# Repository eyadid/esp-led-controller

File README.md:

For more details visit - https://hackaday.io/project/8365-led-matrix-controller

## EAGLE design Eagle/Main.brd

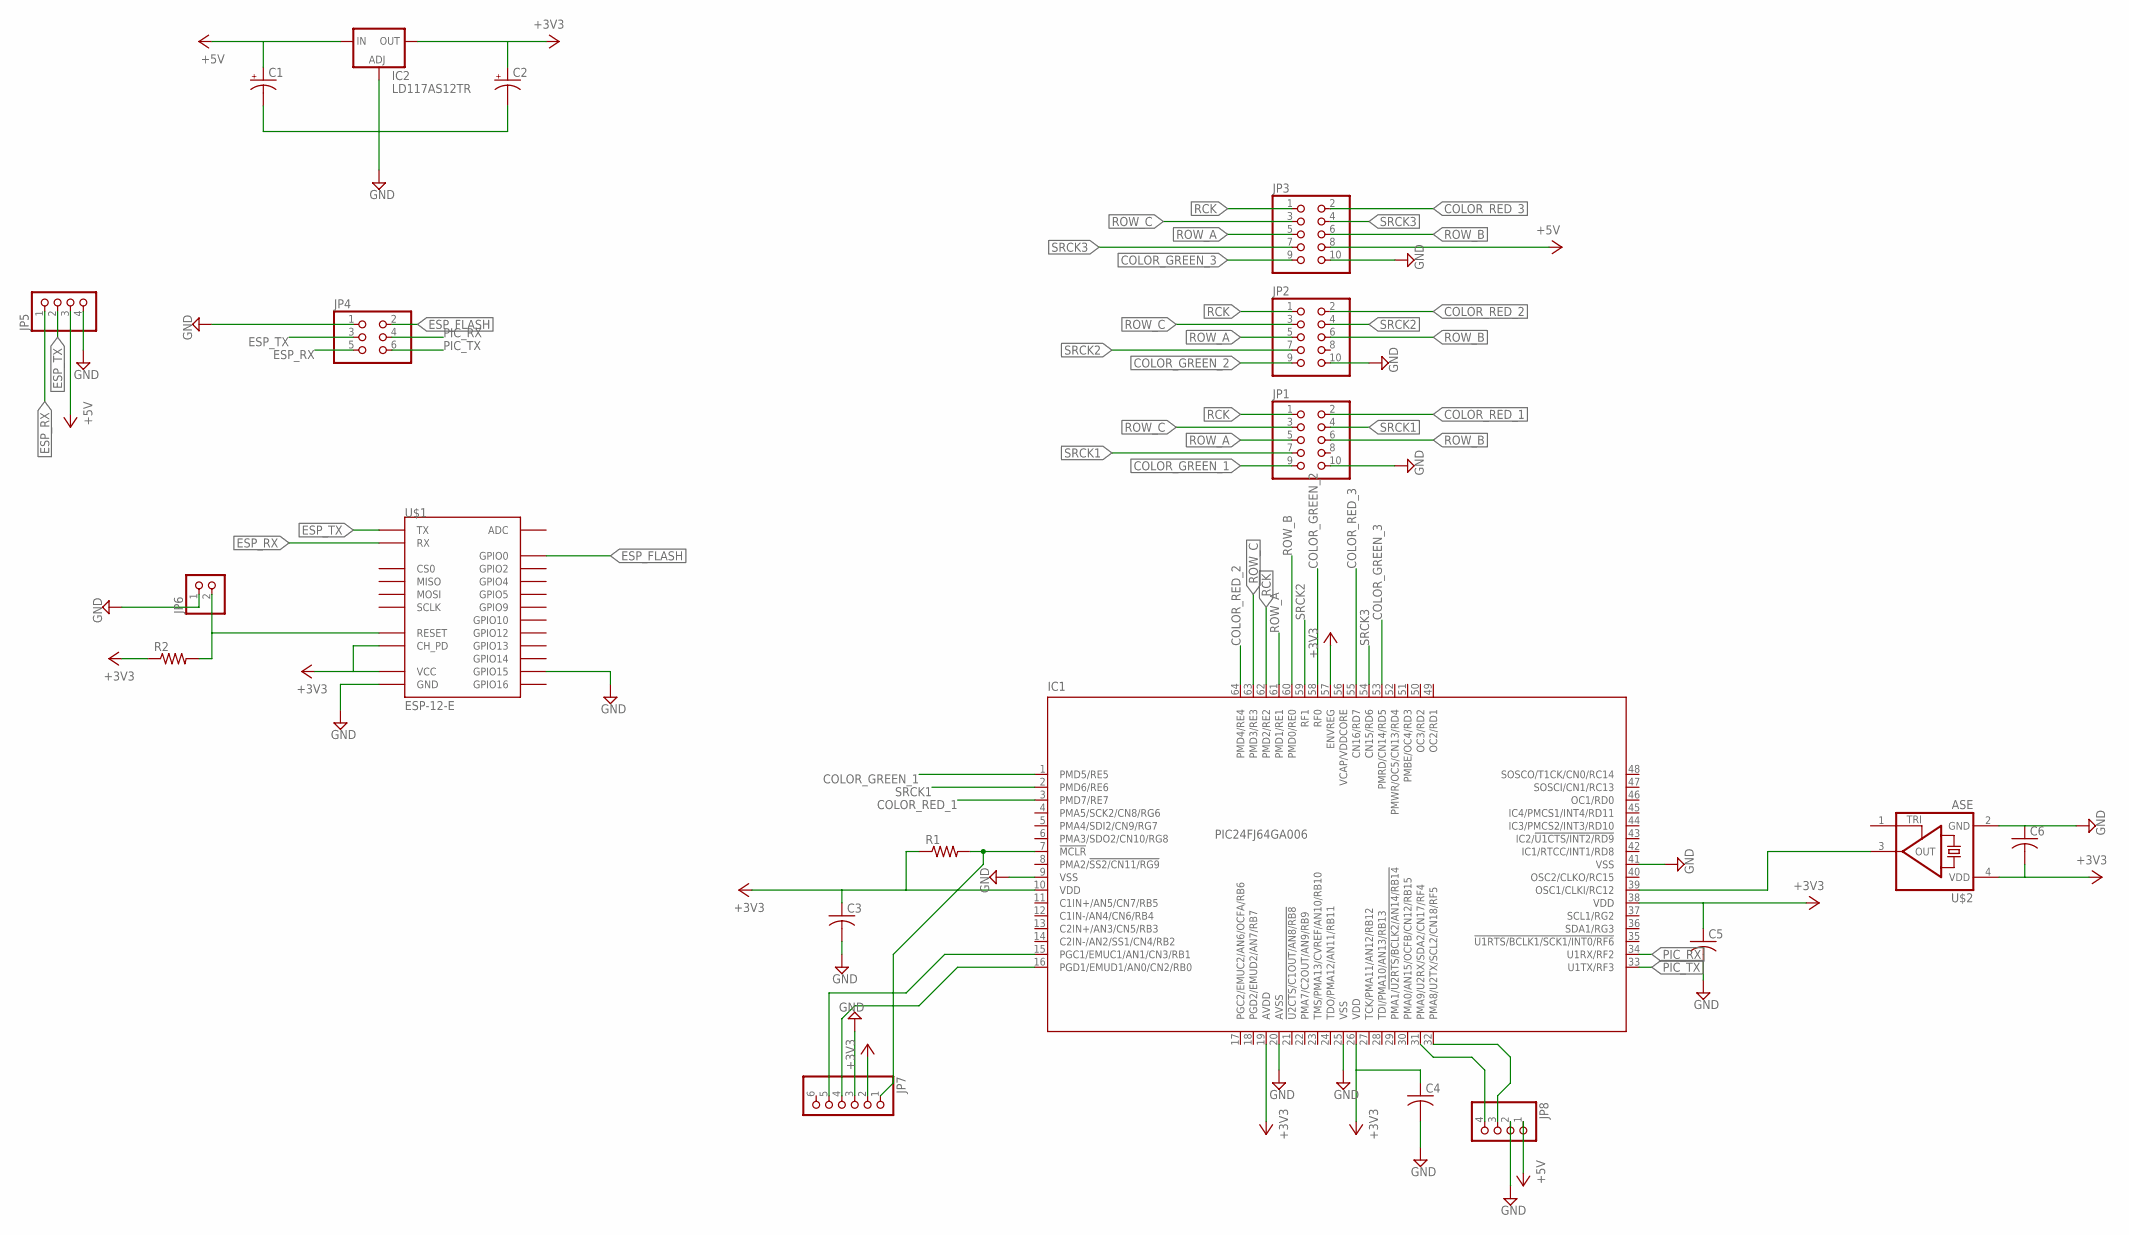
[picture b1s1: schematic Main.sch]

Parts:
C1, C2: CPOL-USB/3528-21W; B/3528-21W
C3, C4, C5, C6: C-USC0603K; C0603K
IC1: PIC24FJ64GA006; TQFP64-10X10
IC2: LD117AS12TR; SOT223
JP1, JP2, JP3: PINHD-2X5; 2X05
JP4: PINHD-2X3; 2X03
JP5, JP8: PINHD-1X4; 1X04
JP6: PINHD-1X2; 1X02
JP7: PINHD-1X6; 1X06
R1, R2: R-US_MELF0102W; MINI_MELF-0102W
U$1: ESP-12-E
U$2: ASE

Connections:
+3V3: C2.+, C3.1, C4.1, C5.1, C6.2, IC1.10 (VDD), IC1.19 (AVDD), IC1.26 (VDD), IC1.38 (VDD), IC1.57 (ENVREG), IC2.4 (OUT), JP7.2, R1.1, R2.1, U$1.CH_PD, U$1.VCC, U$2.4 (VDD)
+5V: C1.+, IC2.3 (IN), JP3.8, JP5.3, JP8.1
COLOR_GREEN_1: IC1.1 (PMD5/RE5), JP1.9
COLOR_GREEN_2: IC1.58 (RF0), JP2.9
COLOR_GREEN_3: IC1.53 (PMRD/CN14/RD5), JP3.9
COLOR_RED_1: IC1.3 (PMD7/RE7), JP1.2
COLOR_RED_2: IC1.64 (PMD4/RE4), JP2.2
COLOR_RED_3: IC1.55 (CN16/RD7), JP3.2
ESP_FLASH: JP4.2, U$1.GPIO0
ESP_RX: JP4.5, JP5.1, U$1.RX
ESP_TX: JP4.3, JP5.2, U$1.TX
GND: C1.-, C2.-, C3.2, C4.2, C5.2, C6.1, IC1.9 (VSS), IC1.20 (AVSS), IC1.25 (VSS), IC1.41 (VSS), IC2.1 (ADJ), JP1.10, JP2.10, JP3.10, JP4.1, JP5.4, JP6.1, JP7.3, JP8.2, U$1.GND, U$1.GPIO15, U$2.2 (GND)
unnamed: IC1.39 (OSC1/CLKI/RC12), U$2.3 (OUT)
unnamed: JP6.2, R2.2, U$1.RESET
unnamed: IC1.15 (PGC1/EMUC1/AN1/CN3/RB1), JP7.5
unnamed: IC1.32 (PMA8/U2TX/SCL2/CN18/RF5), JP8.3
unnamed: IC1.16 (PGD1/EMUD1/AN0/CN2/RB0), JP7.4
unnamed: IC1.31 (PMA9/U2RX/SDA2/CN17/RF4), JP8.4
unnamed: IC1.7 (!MCLR), JP7.1, R1.2
PIC_RX: IC1.34 (U1RX/RF2), JP4.4
PIC_TX: IC1.33 (U1TX/RF3), JP4.6
RCK: IC1.62 (PMD2/RE2), JP1.1, JP2.1, JP3.1
ROW_A: IC1.61 (PMD1/RE1), JP1.5, JP2.5, JP3.5
ROW_B: IC1.60 (PMD0/RE0), JP1.6, JP2.6, JP3.6
ROW_C: IC1.63 (PMD3/RE3), JP1.3, JP2.3, JP3.3
SRCK1: IC1.2 (PMD6/RE6), JP1.4, JP1.7
SRCK2: IC1.59 (RF1), JP2.4, JP2.7
SRCK3: IC1.54 (CN15/RD6), JP3.4, JP3.7

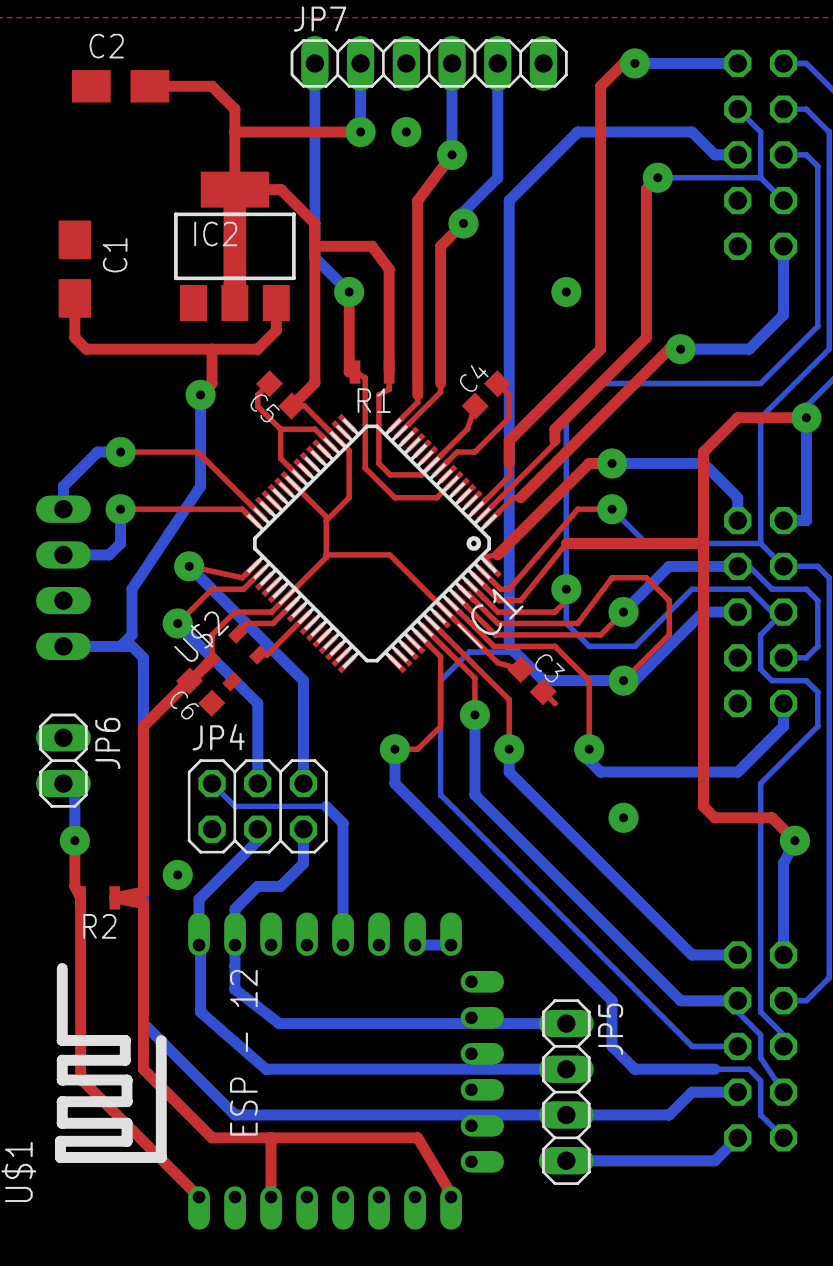
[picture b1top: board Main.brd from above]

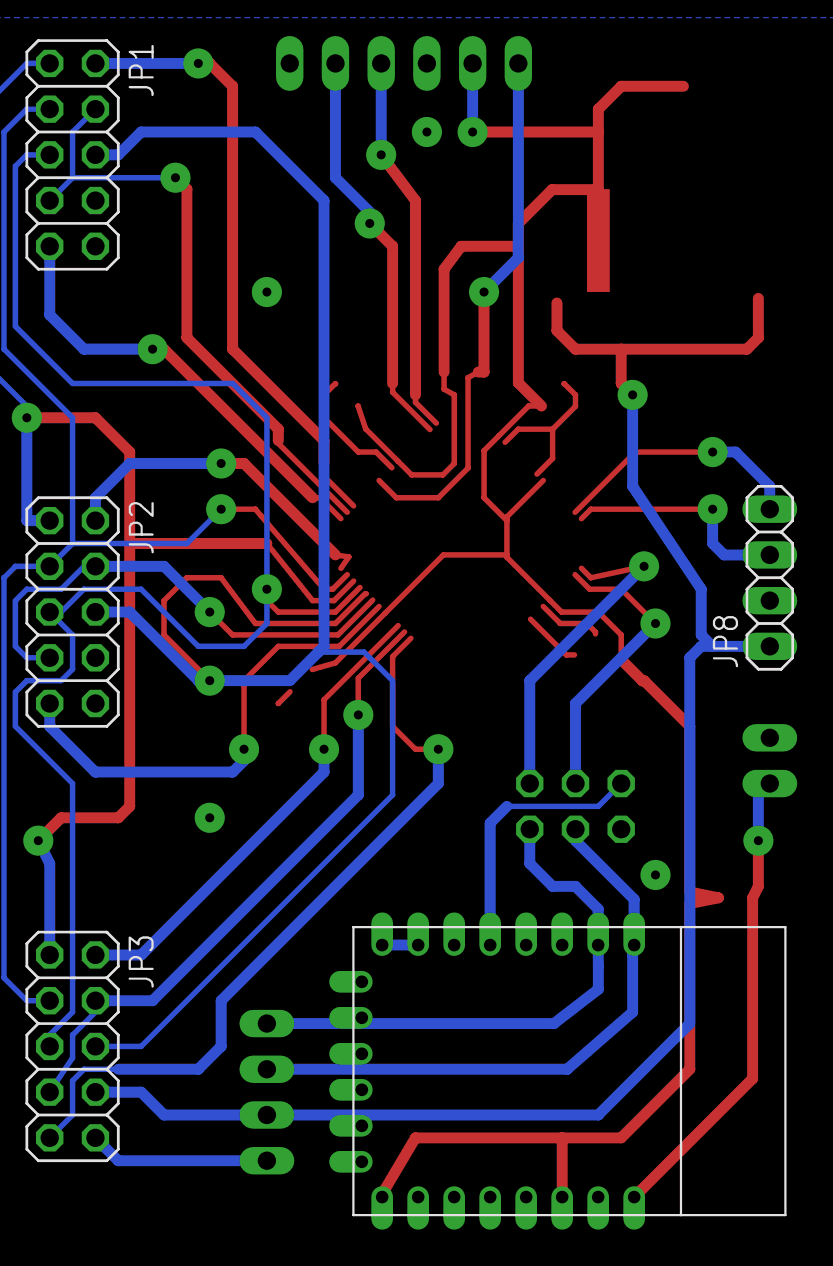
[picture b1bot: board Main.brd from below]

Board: 2 copper layers, 20 parts (4 on the bottom side), 28 nets.

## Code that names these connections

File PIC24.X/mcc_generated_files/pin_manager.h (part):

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*/
/**
  @Summary
    Sets the GPIO pin, RD5, high using LATD5.

  @Description
    Sets the GPIO pin, RD5, high using LATD5.

  @Preconditions
    The RD5 must be set to an output.
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#define IO_RD5_SetHigh()          _LATD5 = 1
/**
  @Summary
    Sets the GPIO pin, RD5, low using LATD5.

  @Description
    Sets the GPIO pin, RD5, low using LATD5.

  @Preconditions
    The RD5 must be set to an output.
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#define IO_RD5_SetLow()           _LATD5 = 0
/**
  @Summary
    Toggles the GPIO pin, RD5, using LATD5.

  @Description
    Toggles the GPIO pin, RD5, using LATD5.

  @Preconditions
    The RD5 must be set to an output.
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#define IO_RD5_Toggle()           _LATD5 ^= 1
/**
  @Summary
    Reads the value of the GPIO pin, RD5.

  @Description
    Reads the value of the GPIO pin, RD5.

  @Preconditions
    None.
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    </code>

*/
#define IO_RD5_GetValue()         _RD5
/**
  @Summary
    Configures the GPIO pin, RD5, as an input.

  @Description
    Configures the GPIO pin, RD5, as an input.

  @Preconditions
    None.
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#define IO_RD5_SetDigitalInput()  _TRISD5 = 1
/**
  @Summary
    Configures the GPIO pin, RD5, as an output.

  @Description
    Configures the GPIO pin, RD5, as an output.

  @Preconditions
    None.
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#define IO_RD5_SetDigitalOutput() _TRISD5 = 0
/**
  @Summary
    Sets the GPIO pin, RD6, high using LATD6.

  @Description
    Sets the GPIO pin, RD6, high using LATD6.

  @Preconditions
    The RD6 must be set to an output.
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#define IO_RD6_SetHigh()          _LATD6 = 1
/**
  @Summary
    Sets the GPIO pin, RD6, low using LATD6.

  @Description
    Sets the GPIO pin, RD6, low using LATD6.

  @Preconditions
    The RD6 must be set to an output.
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#define IO_RD6_SetLow()           _LATD6 = 0
/**
  @Summary
    Toggles the GPIO pin, RD6, using LATD6.

  @Description
    Toggles the GPIO pin, RD6, using LATD6.

  @Preconditions
    The RD6 must be set to an output.
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#define IO_RD6_Toggle()           _LATD6 ^= 1
/**
  @Summary
    Reads the value of the GPIO pin, RD6.

  @Description
    Reads the value of the GPIO pin, RD6.

  @Preconditions
    None.
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    </code>

*/
#define IO_RD6_GetValue()         _RD6
/**
  @Summary
    Configures the GPIO pin, RD6, as an input.

  @Description
    Configures the GPIO pin, RD6, as an input.

  @Preconditions
    None.
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#define IO_RD6_SetDigitalInput()  _TRISD6 = 1
/**
  @Summary
    Configures the GPIO pin, RD6, as an output.

  @Description
    Configures the GPIO pin, RD6, as an output.

  @Preconditions
    None.
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#define IO_RD6_SetDigitalOutput() _TRISD6 = 0
/**
  @Summary
    Sets the GPIO pin, RD7, high using LATD7.

  @Description
    Sets the GPIO pin, RD7, high using LATD7.

  @Preconditions
    The RD7 must be set to an output.
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#define IO_RD7_SetHigh()          _LATD7 = 1
/**
  @Summary
    Sets the GPIO pin, RD7, low using LATD7.

  @Description
    Sets the GPIO pin, RD7, low using LATD7.

  @Preconditions
    The RD7 must be set to an output.
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#define IO_RD7_SetLow()           _LATD7 = 0
/**
  @Summary
    Toggles the GPIO pin, RD7, using LATD7.

  @Description
    Toggles the GPIO pin, RD7, using LATD7.

  @Preconditions
    The RD7 must be set to an output.
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#define IO_RD7_Toggle()           _LATD7 ^= 1
/**
  @Summary
    Reads the value of the GPIO pin, RD7.

  @Description
    Reads the value of the GPIO pin, RD7.

  @Preconditions
    None.
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    </code>

*/
#define IO_RD7_GetValue()         _RD7
/**
  @Summary
    Configures the GPIO pin, RD7, as an input.

  @Description
    Configures the GPIO pin, RD7, as an input.

  @Preconditions
    None.
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#define IO_RD7_SetDigitalInput()  _TRISD7 = 1
/**
  @Summary
    Configures the GPIO pin, RD7, as an output.

  @Description
    Configures the GPIO pin, RD7, as an output.

  @Preconditions
    None.
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#define IO_RD7_SetDigitalOutput() _TRISD7 = 0
/**
  @Summary
    Sets the GPIO pin, RE0, high using LATE0.

  @Description
    Sets the GPIO pin, RE0, high using LATE0.

  @Preconditions
    The RE0 must be set to an output.
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#define IO_RE0_SetHigh()          _LATE0 = 1
/**
  @Summary
    Sets the GPIO pin, RE0, low using LATE0.

  @Description
    Sets the GPIO pin, RE0, low using LATE0.

  @Preconditions
    The RE0 must be set to an output.
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#define IO_RE0_SetLow()           _LATE0 = 0
/**
  @Summary
    Toggles the GPIO pin, RE0, using LATE0.

  @Description
    Toggles the GPIO pin, RE0, using LATE0.

  @Preconditions
    The RE0 must be set to an output.
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#define IO_RE0_Toggle()           _LATE0 ^= 1
/**
  @Summary
    Reads the value of the GPIO pin, RE0.

  @Description
    Reads the value of the GPIO pin, RE0.

  @Preconditions
    None.
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    </code>

*/
#define IO_RE0_GetValue()         _RE0
/**
  @Summary
    Configures the GPIO pin, RE0, as an input.

  @Description
    Configures the GPIO pin, RE0, as an input.

  @Preconditions
    None.
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#define IO_RE0_SetDigitalInput()  _TRISE0 = 1
/**
  @Summary
    Configures the GPIO pin, RE0, as an output.

  @Description
    Configures the GPIO pin, RE0, as an output.

  @Preconditions
    None.
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#define IO_RE0_SetDigitalOutput() _TRISE0 = 0
/**
  @Summary
    Sets the GPIO pin, RE1, high using LATE1.

  @Description
    Sets the GPIO pin, RE1, high using LATE1.

  @Preconditions
    The RE1 must be set to an output.
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#define IO_RE1_SetHigh()          _LATE1 = 1
/**
  @Summary
    Sets the GPIO pin, RE1, low using LATE1.

  @Description
    Sets the GPIO pin, RE1, low using LATE1.

  @Preconditions
    The RE1 must be set to an output.
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#define IO_RE1_SetLow()           _LATE1 = 0
/**
  @Summary
    Toggles the GPIO pin, RE1, using LATE1.

  @Description
    Toggles the GPIO pin, RE1, using LATE1.

  @Preconditions
    The RE1 must be set to an output.
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#define IO_RE1_Toggle()           _LATE1 ^= 1
/**
  @Summary
    Reads the value of the GPIO pin, RE1.

  @Description
    Reads the value of the GPIO pin, RE1.

  @Preconditions
    None.
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    </code>

*/
#define IO_RE1_GetValue()         _RE1
/**
  @Summary
    Configures the GPIO pin, RE1, as an input.

  @Description
    Configures the GPIO pin, RE1, as an input.

  @Preconditions
    None.
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#define IO_RE1_SetDigitalInput()  _TRISE1 = 1
/**
  @Summary
    Configures the GPIO pin, RE1, as an output.

  @Description
    Configures the GPIO pin, RE1, as an output.

  @Preconditions
    None.
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#define IO_RE1_SetDigitalOutput() _TRISE1 = 0
/**
  @Summary
    Sets the GPIO pin, RE2, high using LATE2.

  @Description
    Sets the GPIO pin, RE2, high using LATE2.

  @Preconditions
    The RE2 must be set to an output.
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#define IO_RE2_SetHigh()          _LATE2 = 1
/**
  @Summary
    Sets the GPIO pin, RE2, low using LATE2.

  @Description
    Sets the GPIO pin, RE2, low using LATE2.

  @Preconditions
    The RE2 must be set to an output.
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#define IO_RE2_SetLow()           _LATE2 = 0
/**
  @Summary
    Toggles the GPIO pin, RE2, using LATE2.

  @Description
    Toggles the GPIO pin, RE2, using LATE2.

  @Preconditions
    The RE2 must be set to an output.
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#define IO_RE2_Toggle()           _LATE2 ^= 1
/**
  @Summary
    Reads the value of the GPIO pin, RE2.

  @Description
    Reads the value of the GPIO pin, RE2.

  @Preconditions
    None.
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    </code>

*/
#define IO_RE2_GetValue()         _RE2
/**
  @Summary
    Configures the GPIO pin, RE2, as an input.

  @Description
    Configures the GPIO pin, RE2, as an input.

  @Preconditions
    None.
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#define IO_RE2_SetDigitalInput()  _TRISE2 = 1
/**
  @Summary
    Configures the GPIO pin, RE2, as an output.

  @Description
    Configures the GPIO pin, RE2, as an output.

  @Preconditions
    None.
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#define IO_RE2_SetDigitalOutput() _TRISE2 = 0
/**
  @Summary
    Sets the GPIO pin, RE3, high using LATE3.

  @Description
    Sets the GPIO pin, RE3, high using LATE3.

  @Preconditions
    The RE3 must be set to an output.
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#define IO_RE3_SetHigh()          _LATE3 = 1
/**
  @Summary
    Sets the GPIO pin, RE3, low using LATE3.

  @Description
    Sets the GPIO pin, RE3, low using LATE3.

  @Preconditions
    The RE3 must be set to an output.
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#define IO_RE3_SetLow()           _LATE3 = 0
/**
  @Summary
    Toggles the GPIO pin, RE3, using LATE3.

  @Description
    Toggles the GPIO pin, RE3, using LATE3.

  @Preconditions
    The RE3 must be set to an output.
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#define IO_RE3_Toggle()           _LATE3 ^= 1
/**
  @Summary
    Reads the value of the GPIO pin, RE3.

  @Description
    Reads the value of the GPIO pin, RE3.

  @Preconditions
    None.
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    </code>

*/
#define IO_RE3_GetValue()         _RE3
/**
  @Summary
    Configures the GPIO pin, RE3, as an input.

  @Description
    Configures the GPIO pin, RE3, as an input.

  @Preconditions
    None.
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#define IO_RE3_SetDigitalInput()  _TRISE3 = 1
/**
  @Summary
    Configures the GPIO pin, RE3, as an output.

  @Description
    Configures the GPIO pin, RE3, as an output.

  @Preconditions
    None.
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#define IO_RE3_SetDigitalOutput() _TRISE3 = 0
/**
  @Summary
    Sets the GPIO pin, RE4, high using LATE4.

  @Description
    Sets the GPIO pin, RE4, high using LATE4.

  @Preconditions
    The RE4 must be set to an output.
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
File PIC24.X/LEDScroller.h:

/* 
 * File:   LEDScroller.h
 * Author: Yadid
 *
 * Created on August 12, 2015, 8:18 PM
 */

#include "SystemConfiguration.h"



#ifndef LEDSCROLLER_H
#define	LEDSCROLLER_H

#ifdef	__cplusplus
extern "C" {
#endif

#define RCK               LATEbits.LATE2

#define SRCK              LATEbits.LATE6
#define COLOR_BIT_GREEN_1 LATEbits.LATE5
#define COLOR_BIT_RED_1   LATEbits.LATE7

#define SRCK2             LATFbits.LATF1
#define COLOR_BIT_GREEN_2 LATFbits.LATF0
#define COLOR_BIT_RED_2   LATEbits.LATE4

#define SRCK3             LATDbits.LATD6
#define COLOR_BIT_GREEN_3 LATDbits.LATD5
#define COLOR_BIT_RED_3   LATDbits.LATD7

#define ROW_A             LATEbits.LATE1
#define ROW_B             LATEbits.LATE0
#define ROW_C             LATEbits.LATE3

#define BLINK_TOTAL 600
#define BLINK_SWITCH 300

#define ROWS_COUNT_3

#define LETTERS_COUNT 250
#define LETTER_HEIGHT 10

#define COLOR_OFF           0
#define COLOR_RED           1
#define COLOR_GREEN         2
#define COLOR_ORANGE        3
#define COLOR_BLINK_RED     4
#define COLOR_BLINK_GREEN   8
#define COLOR_BLINK_ORANGE  12

#define DISPLAY_WIDTH       160
#define DISPLAY_WORDS       (DISPLAY_WIDTH / 8)
#define DISPLAY_ROWS        3
#define DISPLAY_ROW_HEIGHT  8

extern void LED_InitScroller();

extern void LED_SetColor(uint8_t color);
extern void LED_WriteText(const uint8_t *text);
extern void LED_Paint();
extern void LED_Clear();

#ifdef	__cplusplus
}
#endif

#endif	/* LEDSCROLLER_H */



/*

*/

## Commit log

2015-11-08 First Rev.
2015-11-08 Readme
2015-11-08 Control Page
2015-11-09 Slack Bot

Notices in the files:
PIC24.X/mcc_generated_files/pin_manager.h:
Copyright (c) 2013 - 2015 released Microchip Technology Inc.  All rights reserved.
